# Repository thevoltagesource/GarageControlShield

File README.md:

# Garage Control PCB
## Wemos D1 Mini Shield to control one or two garage doors.

Last year I made my 30 year old dumb garage door opener a bit smarter by adding a wifi connected button and sensor.
I have wanted to move from my prototype board to a proper PCB to make it look nicer, practice some SMD soldering, 
and get some more PCB layout experience. This is the fulfillment of those desires.

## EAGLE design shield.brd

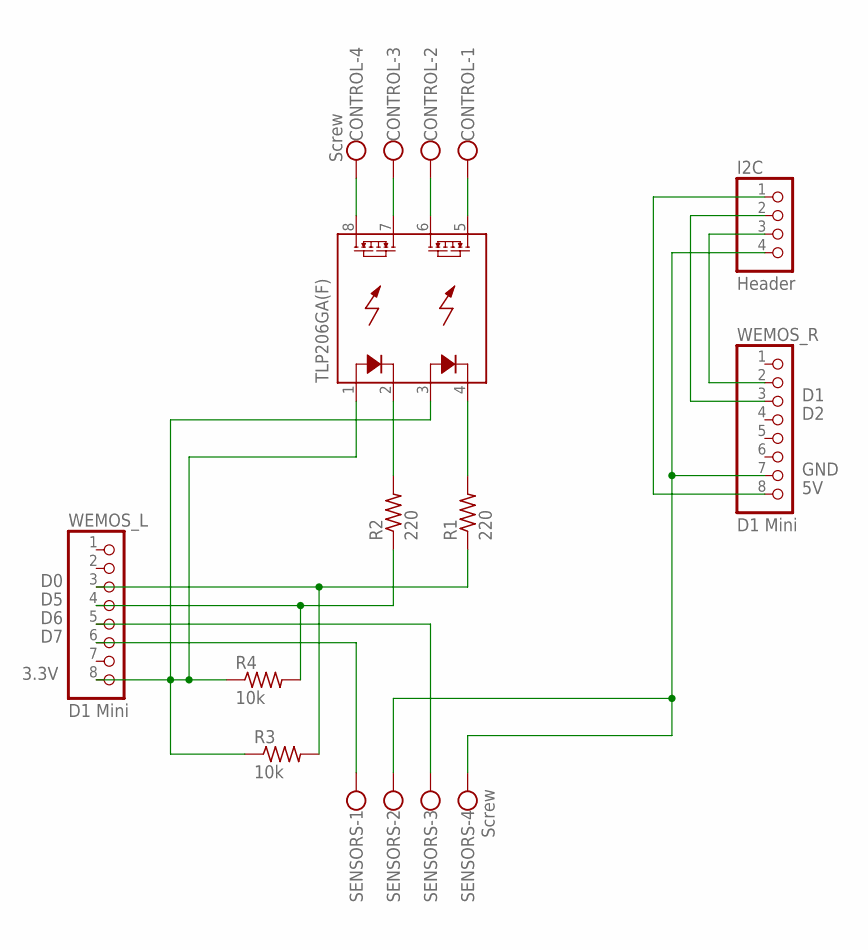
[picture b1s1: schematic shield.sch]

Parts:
CONTROL: Screw; AK500/4-N
I2C: Header; 1X04/OCT
R1, R2: 220; R0603
R3, R4: 10k; R0603
SENSORS: Screw; AK500/4-N
TLP206GA(F): TLP206A; SOP08; MPN TLP206GA(F)
WEMOS_L: D1 Mini; 1X08/OCT
WEMOS_R: D1 Mini; 1X08/OCT

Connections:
3.3V: R3.1, R4.1, TLP206GA(F).1 (LED(+)_1), TLP206GA(F).3 (LED(+)_2), WEMOS_L.8
5V: I2C.1, WEMOS_R.8
D0: R1.1, R3.2, WEMOS_L.3
D1: I2C.2, WEMOS_R.3
D2: I2C.3, WEMOS_R.2
D5: R2.1, R4.2, WEMOS_L.4
D6: SENSORS.3, WEMOS_L.5
D7: SENSORS.1, WEMOS_L.6
GND: I2C.4, SENSORS.2, SENSORS.4, WEMOS_R.7
unnamed: CONTROL.1, TLP206GA(F).5 (RELAY2_1)
unnamed: CONTROL.3, TLP206GA(F).7 (RELAY1_1)
unnamed: CONTROL.2, TLP206GA(F).6 (RELAY2_2)
unnamed: R2.2, TLP206GA(F).2 (LED(-)_1)
unnamed: CONTROL.4, TLP206GA(F).8 (RELAY1_2)
unnamed: R1.2, TLP206GA(F).4 (LED(-)_2)

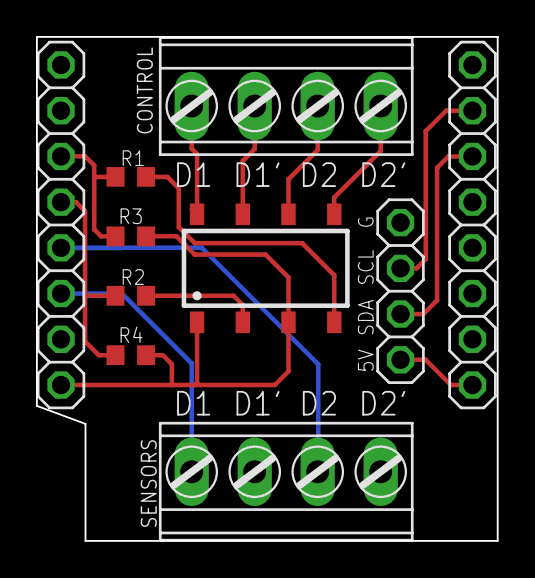
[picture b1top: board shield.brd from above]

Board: 2 copper layers, 25.6 x 28.0 mm, 10 parts (0 on the bottom side), 15 nets.

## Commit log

2019-09-22 Initial commit.
2019-09-22 Added OSHPark cam file.
2019-10-04 Tweak layout and add lables
2019-10-04 tweak silkscreen and add some missing files
2019-12-15 Gerbers for v1.0
2019-12-15 Changed to active low, changed chip, updated silkscreen
2019-12-15 Fix silkscreen for I2C, update values in schematic.
